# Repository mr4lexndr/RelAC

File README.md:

[![CC BY-NC-SA 4.0][cc-by-nc-sa-shield]][cc-by-nc-sa]

This work is licensed under a
[Creative Commons Attribution-NonCommercial-ShareAlike 4.0 International License][cc-by-nc-sa].

[![CC BY-NC-SA 4.0][cc-by-nc-sa-image]][cc-by-nc-sa]

[cc-by-nc-sa]: http://creativecommons.org/licenses/by-nc-sa/4.0/
[cc-by-nc-sa-image]: https://licensebuttons.net/l/by-nc-sa/4.0/88x31.png
[cc-by-nc-sa-shield]: https://img.shields.io/badge/License-CC%20BY--NC--SA%204.0-lightgrey.svg
# RelAC

HomeKit 2-channel Relay module with mains Switch Input based on the [HomeSpan](https://github.com/HomeSpan/HomeSpan) library. It is mainly intended to be used with mains voltage appliances controlled in parallel with the Home app and physical switch. It could be hidden e.g. behind a wall light switch.

## Main Features
- Mains Supply 100-240 Vac
- Status LED and Control push button for easy configuration
- 2 latching relays for low power consumption and thermal emmisions
- 2 live inputs
- Small form factor to be hidden behind the wall light switch.
- Can be configured as single channel device to save cost
  
### Switching Relays
- High quality, low wear Panasonic ADW1203HLW  
- Switching Capacity 16A @ 277V AC  
- Contact material AgSnO2 to minimise arcing  

## User Integration with HomeSpan
Status LED and Control Button are attached to deafault pins for most of the boards. S1 Button is also used as boot button during programming
- LED `GPIO2`
- Button `GPIO0`

## Pinout
Pin assignment for relays and switch inputs. For single channel version only `RELAY 1` and `SWITCH 2` are used.

- RELAY 1
  -  on `GPIO27`
  - off `GPIO26`
- RELAY 2 
  - on `GPIO33`
  - off `GPIO32`
- MAINS INPUT
  - switch 1 `GPIO16`
  - switch 2 `GPIO13`

## User Guide
The setup procedure and configuration can be found [here](https://github.com/HomeSpan/HomeSpan/blob/master/docs/UserGuide.md)

## To Do

- [ ] finish 3D printed case
- [ ] reduce footprint with next revision
- [ ] change layout of programming pins and add RTS support

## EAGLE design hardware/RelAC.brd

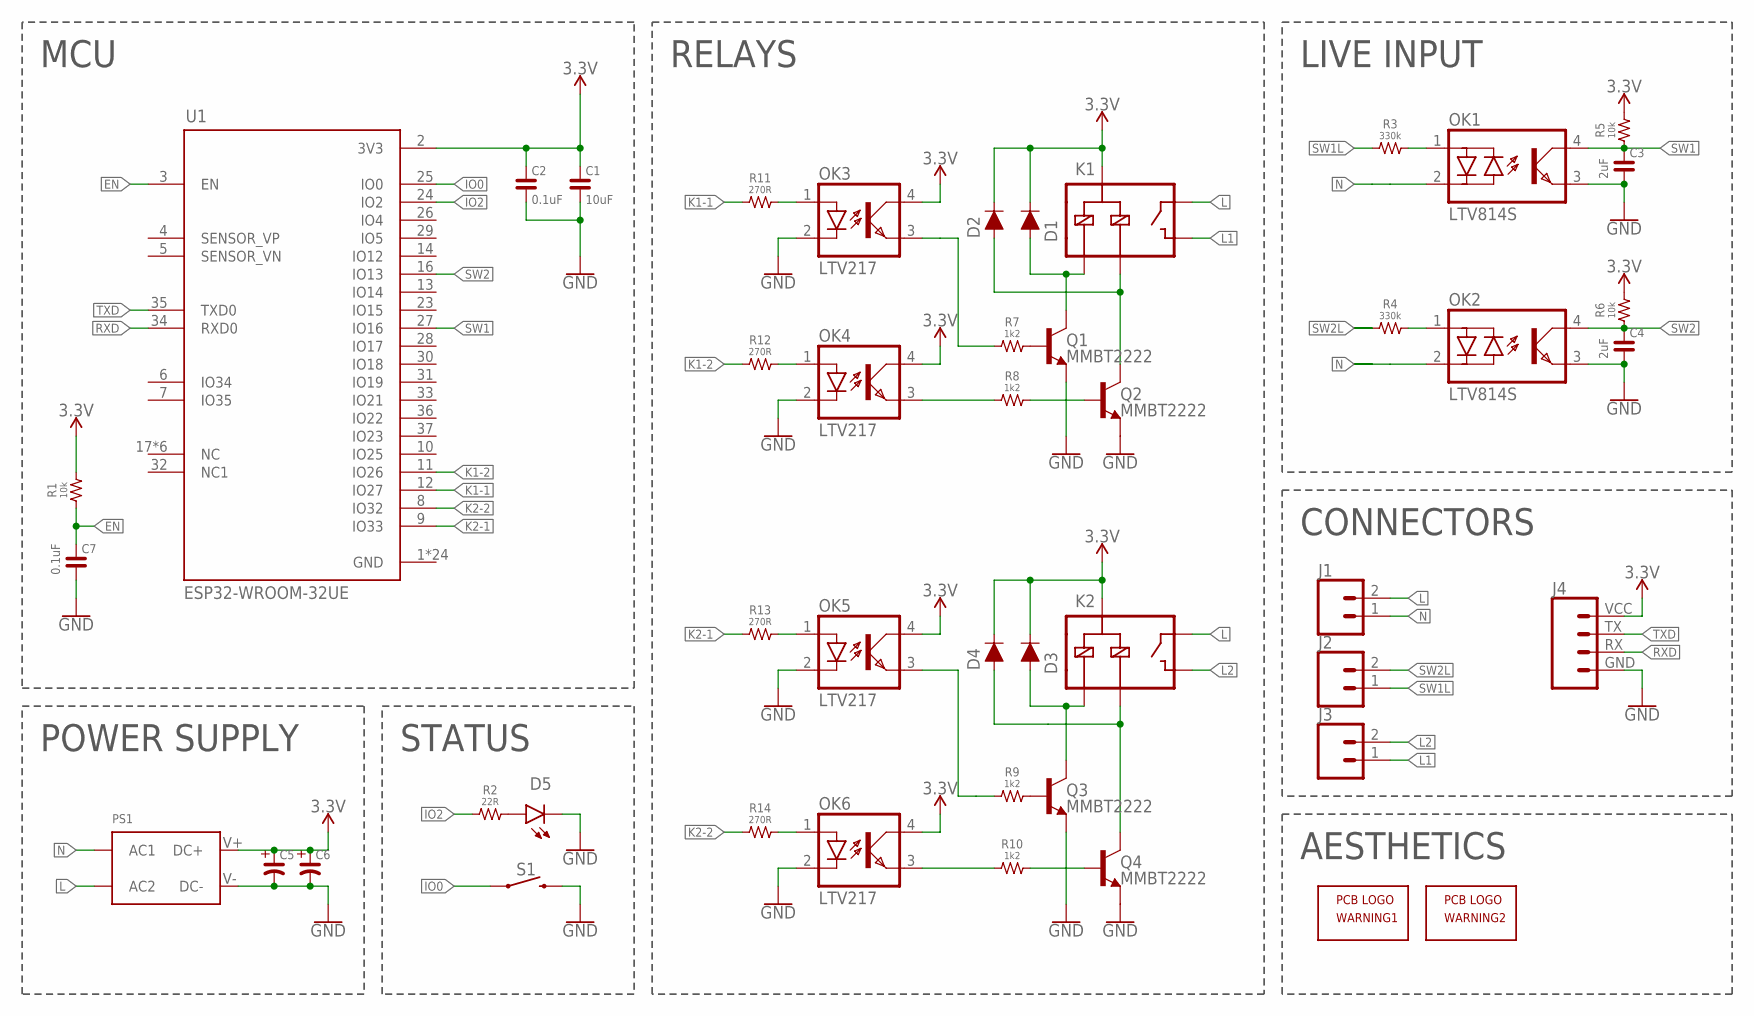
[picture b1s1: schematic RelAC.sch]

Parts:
C1: 10uF; 0805
C2, C7: 0.1uF; 0603
C3, C4: 2uF; 0805
C5, C6: CAP-POLAR-THT_2.5MM-W; CPOL-RADIAL-2.5MM-6.5MM
D1, D2, D3, D4: DIODE-SOD323; SOD-323
D5: LED-ANGLE-2MM
J1, J2, J3: CONN_02-5MM-SCREWTERMINAL; SCREWTERMINAL-5MM-2-DIBO
J4: CONN_04-UART-SMD; UART
K1, K2: RELAY-SPST-LATCHING; RELAY-PANASONIC-ADW1203HLW
OK1, OK2: LTV814S; DIL4-SMD-SMALL
OK3, OK4, OK5, OK6: LTV217; MINI-FLAT-4
PS1: POWER-SUPPLY-HI-LINK-5W; HI-LINK-POWER-SUPPLY
Q1, Q2, Q3, Q4: MMBT2222; SOT23-3
R1, R5, R6: 10k; 0603
R2: 22R; 0603
R3, R4: 330k; 0805
R7, R8, R9, R10: 1k2; 0603
R11, R12, R13, R14: 270R; 0603
S1: MOMENTARY-SWITCH-SPST-PTH-RIGHT-ANGLE-KIT; TACTILE_SWITCH_PTH_RIGHT_ANGLE_KIT
U1: ESP32-WROOM-32UE; MODULE_ESP32-WROOM-32UE(M113EH6400UH3Q0)
WARNING1, WARNING2: PCB-GRAPHICS-HIGH-VOLTAGE; HIGH-VOLTAGE

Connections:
3.3V: C1.2, C2.2, C5.+, C6.+, D1.C, D2.C, D3.C, D4.C, J4.VCC (4), K1.COILM (COIL-COM), K2.COILM (COIL-COM), OK3.4 (COL), OK4.4 (COL), OK5.4 (COL), OK6.4 (COL), PS1.V+ (DC+), R1.2, R5.2, R6.2, U1.2 (3V3)
EN: C7.2, R1.1, U1.3 (EN)
GND: C1.1, C2.1, C3.1, C4.1, C5.-, C6.-, C7.1, D5.C, J4.GND (1), OK1.3 (EMIT), OK2.3 (EMIT), OK3.2 (C), OK4.2 (C), OK5.2 (C), OK6.2 (C), PS1.V- (DC-), Q1.2 (E), Q2.2 (E), Q3.2 (E), Q4.2 (E), S1.2, U1.1 (GND), U1.15 (GND), U1.38 (GND), U1.39_1 (GND), U1.39_2 (GND), U1.39_3 (GND), U1.39_4 (GND), U1.39_5 (GND), U1.39_6 (GND), U1.39_7 (GND), U1.39_8 (GND), U1.39_9 (GND), U1.39_10 (GND), U1.39_11 (GND), U1.39_12 (GND), U1.39_13 (GND), U1.39_14 (GND), U1.39_15 (GND), U1.39_16 (GND), U1.39_17 (GND), U1.39_18 (GND), U1.39_19 (GND), U1.39_20 (GND), U1.39_21 (GND)
IO0: S1.1, U1.25 (IO0)
IO2: R2.1, U1.24 (IO2)
K1-1: R11.1, U1.12 (IO27)
K1-2: R12.1, U1.11 (IO26)
K2-1: R13.1, U1.9 (IO33)
K2-2: R14.1, U1.8 (IO32)
L: J1.2, K1.POLE, K2.POLE, PS1.AC2
L1: J3.1, K1.NO
L2: J3.2, K2.NO
N: J1.1, OK1.2 (C), OK2.2 (C), PS1.AC1
unnamed: D2.A, K1.COIL2, Q2.3 (C)
unnamed: D1.A, K1.COIL1, Q1.3 (C)
unnamed: OK1.1 (A), R3.2
unnamed: D5.A, R2.2
unnamed: OK2.1 (A), R4.2
unnamed: Q1.1 (B), R7.2
unnamed: Q2.1 (B), R8.2
unnamed: OK3.3 (EMIT), R7.1
unnamed: OK4.3 (EMIT), R8.1
unnamed: D3.A, K2.COIL1, Q3.3 (C)
unnamed: D4.A, K2.COIL2, Q4.3 (C)
unnamed: Q3.1 (B), R9.2
unnamed: Q4.1 (B), R10.2
unnamed: OK6.3 (EMIT), R10.1
unnamed: OK5.3 (EMIT), R9.1
unnamed: OK6.1 (A), R14.2
unnamed: OK5.1 (A), R13.2
unnamed: OK4.1 (A), R12.2
unnamed: OK3.1 (A), R11.2
RXD: J4.RX (2), U1.34 (RXD0)
SW1: C3.2, OK1.4 (COL), R5.1, U1.27 (IO16)
SW1L: J2.1, R3.1
SW2: C4.2, OK2.4 (COL), R6.1, U1.16 (IO13)
SW2L: J2.2, R4.1
TXD: J4.TX (3), U1.35 (TXD0)

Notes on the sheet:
MCU
RELAYS
LIVE INPUT
STATUS
POWER SUPPLY
CONNECTORS
AESTHETICS

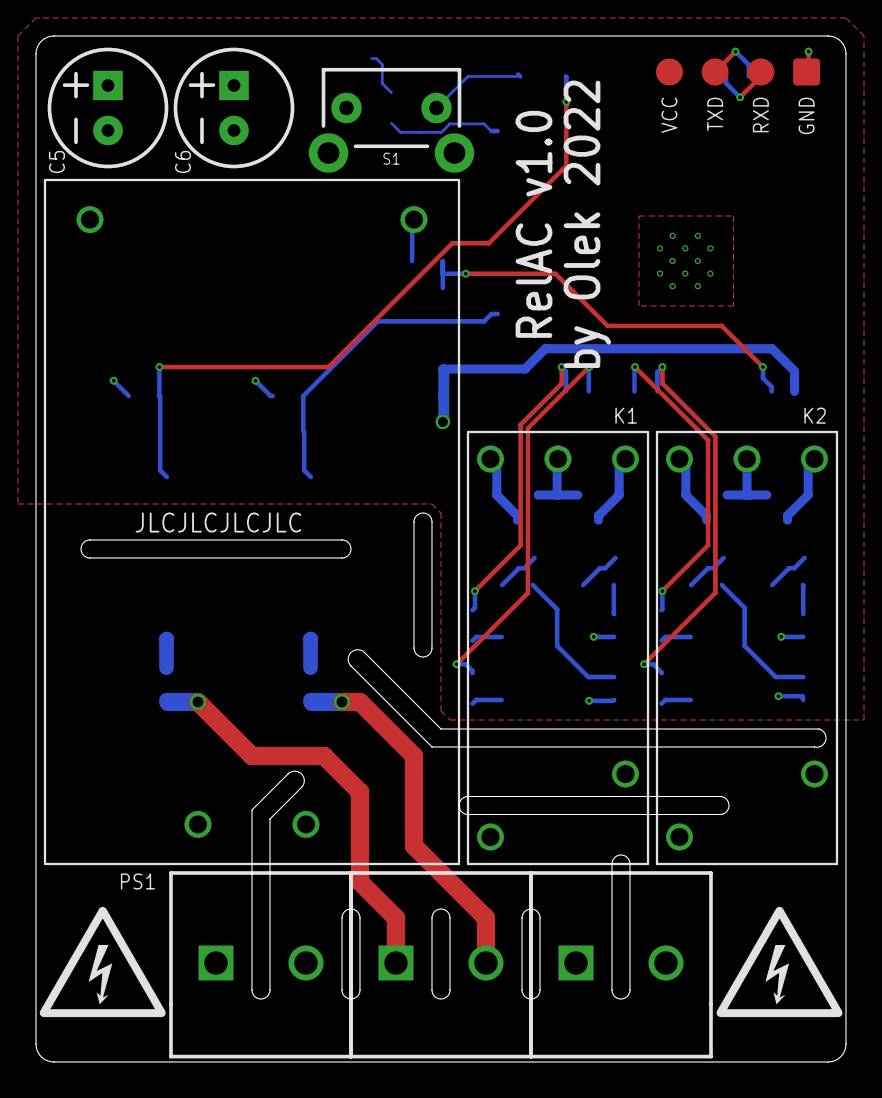
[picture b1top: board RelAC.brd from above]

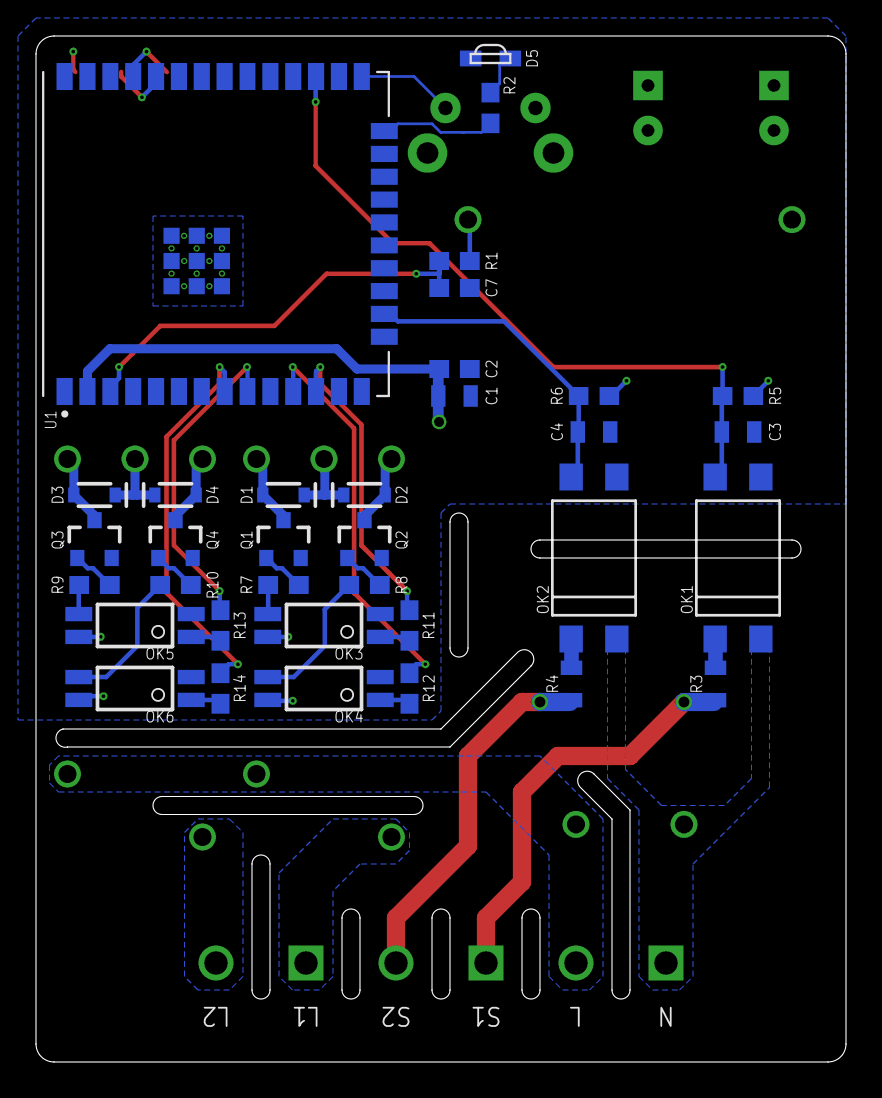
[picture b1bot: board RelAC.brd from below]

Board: 2 copper layers, 45.0 x 57.0 mm, 47 parts (35 on the bottom side), 38 nets.

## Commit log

2023-02-13 add documentation
2023-03-02 update assets

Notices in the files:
parts and their libraries:
SparkFun-PowerSymbols: Licensing: Creative Commons ShareAlike 4.0 International - https://creativecommons.org/licenses/by-sa/4.0
